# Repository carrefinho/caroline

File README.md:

# Caroline

Caroline is a 36-key unibody split electrostatic capacitive (EC) keyboard featuring Direct EC: the key matrix is read directly by the microcontroller's ADC, without using any external components.

> Her name is Caroline. Remember that!

> [!WARNING]
> This is a work in progress.

## Design

- Minimal BOM EC sensing: no mux, op-amp, integrator cap, no nothing
- 36-key Treadstone staggered layout with QAZlice characteristics
- Seeed Studio XIAO **Plus** controller on ZMK firmware
    - nRF52840 Plus for wireless, SAMD21 Plus or RP2040 Plus for wired
- Low-power wireless with nRF52840
    - Over a month of battery life on 100 mAh, a fraction of the power draw of other wireless EC keyboards
    - Idle scan draws under 30µA, always ready to type with no wake-up delay
- Plate designed for Deskeys (DES) housings

## Direct EC

## Files

- [`caroline-pcb/`](caroline-pcb/): KiCad project
    - [View the PCB on KiCanvas](https://kicanvas.org/?github=https%3A%2F%2Fgithub.com%2Fcarrefinho%2Fcaroline%2Ftree%2Fmain%2Fcaroline-pcb)
- [`ergogen/`](ergogen/): Ergogen config that generates key positions and reference outlines
- [`tools/`](tools/): helper scripts
    - [`pick_screws.py`](tools/pick_screws.py): picks optimal screw pattern for an even clamp (see [`caroline-pcb/`](caroline-pcb/README.md#screw-holes))

## Build Guide

## Firmware

## Credits

- [dohn-joh/heatwave](https://github.com/dohn-joh/heatwave): layout, aesthetics, ergogen reference
- [apfel/daertwing](https://git.clacktal.es/apfel/daertwing/): layout reference
- [Madeline](https://40s.wiki/boards/madeline): aesthetics
- [Marbelymarble/Adalyn](https://github.com/Marbelymarble/Adalyn): layout reference for early experiments

## License

[CERN-OHL-P v2](LICENSE)

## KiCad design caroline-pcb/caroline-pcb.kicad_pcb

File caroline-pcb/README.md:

# PCB

KiCad 10 project. Footprints, symbols and the XIAO 3D model are in [`lib/`](lib/).

## Screw holes

The PCB is screwed to the plate, clamping the housings and dome flanges between them, so where the screws go decides how evenly every key is clamped, which matters for EC since you want every dome to be equally snug against the PCB.

The board has 42 M2 holes, but only the 20 with a silk ring on the back are used. 20 seemed a reasonable compromise between an even clamp and ease of assembly. [`tools/pick_screws.py`](../tools/pick_screws.py) chose them. It tries every combination of holes, mirrored left to right, and keeps the one where keys and the outer edge are, on average, closest to a screw.

To re-pick, close the project in KiCad and run:

```sh
uv run tools/pick_screws.py -n 20 --apply
```

This moves the rings to the new picks on the board and in the schematic, and writes a plot comparing them to the current set.

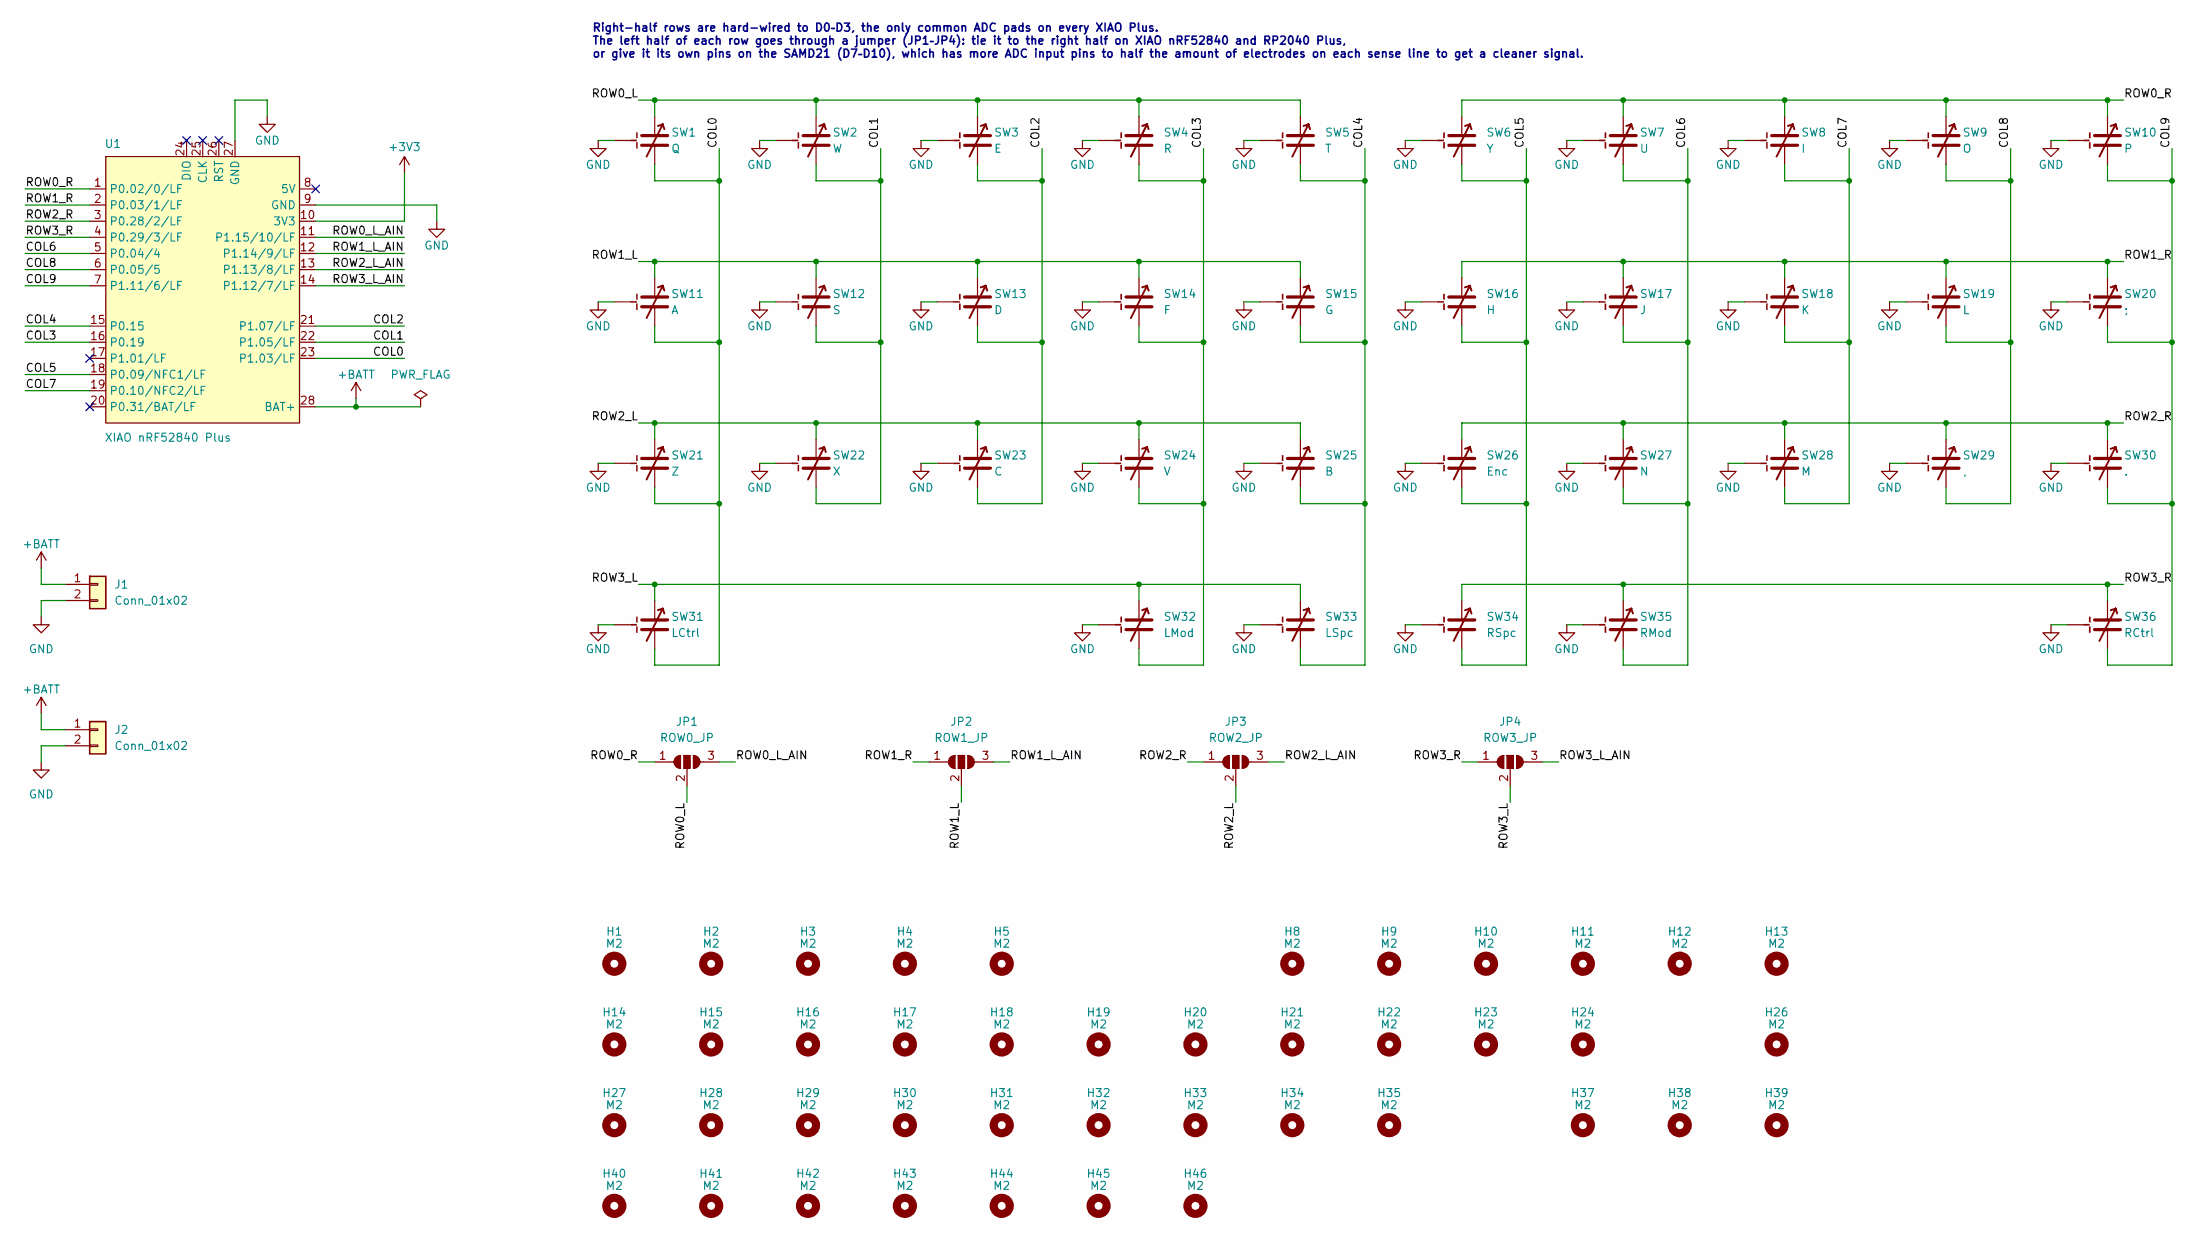
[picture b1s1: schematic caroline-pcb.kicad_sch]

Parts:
H1, H3, H5, H8, H10, H12, H15, H17, H20, H22, H26, H28, H33, H35, H37, H39, H41, H42, H44, H46: M2; MountingHole_2.2mm_M2_ring_silk
H2, H4, H9, H11, H13, H14, H16, H18, H19, H21, H23, H24, H27, H29, H30, H31, H32, H34, H38, H40, H43, H45: M2; MountingHole_2.2mm_M2
J1, J2: Conn_01x02; PinHeader_1x02_P2.54mm_Vertical
JP1: ROW0_JP; SolderJumper-3_P1.3mm_Open_RoundedPad1.0x1.5mm
JP2: ROW1_JP; SolderJumper-3_P1.3mm_Open_RoundedPad1.0x1.5mm
JP3: ROW2_JP; SolderJumper-3_P1.3mm_Open_RoundedPad1.0x1.5mm
JP4: ROW3_JP; SolderJumper-3_P1.3mm_Open_RoundedPad1.0x1.5mm
SW1: Q; EC_Topre_1U_ViaSP
SW2: W; EC_Topre_1U_ViaSP
SW3: E; EC_Topre_1U_ViaSP
SW4: R; EC_Topre_1U_ViaSP
SW5: T; EC_Topre_1U_ViaSP
SW6: Y; EC_Topre_1U_ViaSP
SW7: U; EC_Topre_1U_ViaSP
SW8: I; EC_Topre_1U_ViaSP
SW9: O; EC_Topre_1U_ViaSP
SW10: P; EC_Topre_1U_ViaSP
SW11: A; EC_Topre_1U_ViaSP
SW12: S; EC_Topre_1U_ViaSP
SW13: D; EC_Topre_1U_ViaSP
SW14: F; EC_Topre_1U_ViaSP
SW15: G; EC_Topre_1U_ViaSP
SW16: H; EC_Topre_1U_ViaSP
SW17: J; EC_Topre_1U_ViaSP
SW18: K; EC_Topre_1U_ViaSP
SW19: L; EC_Topre_1U_ViaSP
SW20: ;; EC_Topre_1U_ViaSP
SW21: Z; EC_Topre_1U_ViaSP
SW22: X; EC_Topre_1U_ViaSP
SW23: C; EC_Topre_1U_ViaSP
SW24: V; EC_Topre_1U_ViaSP
SW25: B; EC_Topre_1U_ViaSP
SW26: Enc; EC_Topre_1U_ViaSP
SW27: N; EC_Topre_1U_ViaSP
SW28: M; EC_Topre_1U_ViaSP
SW29: ,; EC_Topre_1U_ViaSP
SW30: .; EC_Topre_1U_ViaSP
SW31: LCtrl; EC_Topre_1U_ViaSP
SW32: LMod; EC_Topre_1U_ViaSP
SW33: LSpc; EC_Topre_1U_ViaSP
SW34: RSpc; EC_Topre_1U_ViaSP
SW35: RMod; EC_Topre_1U_ViaSP
SW36: RCtrl; EC_Topre_1U_ViaSP
U1: XIAO nRF52840 Plus; Xiao_nRF52840_Plus

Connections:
+3V3: U1.10 (3V3)
+BATT: J1.1, J2.1, U1.28 (BAT+)
/COL0: SW1.2, SW11.2, SW21.2, SW31.2, U1.23 (P1.03/LF)
/COL1: SW2.2, SW12.2, SW22.2, U1.22 (P1.05/LF)
/COL2: SW3.2, SW13.2, SW23.2, U1.21 (P1.07/LF)
/COL3: SW4.2, SW14.2, SW24.2, SW32.2, U1.16 (P0.19)
/COL4: SW5.2, SW15.2, SW25.2, SW33.2, U1.15 (P0.15)
/COL5: SW6.2, SW16.2, SW26.2, SW34.2, U1.18 (P0.09/NFC1/LF)
/COL6: SW7.2, SW17.2, SW27.2, SW35.2, U1.5 (P0.04/4)
/COL7: SW8.2, SW18.2, SW28.2, U1.19 (P0.10/NFC2/LF)
/COL8: SW9.2, SW19.2, SW29.2, U1.6 (P0.05/5)
/COL9: SW10.2, SW20.2, SW30.2, SW36.2, U1.7 (P1.11/6/LF)
/ROW0_L: JP1.2 (C), SW1.1 (S), SW2.1 (S), SW3.1 (S), SW4.1 (S), SW5.1 (S)
/ROW0_L_AIN: JP1.3 (B), U1.11 (P1.15/10/LF)
/ROW0_R: JP1.1 (A), SW6.1 (S), SW7.1 (S), SW8.1 (S), SW9.1 (S), SW10.1 (S), U1.1 (P0.02/0/LF)
/ROW1_L: JP2.2 (C), SW11.1 (S), SW12.1 (S), SW13.1 (S), SW14.1 (S), SW15.1 (S)
/ROW1_L_AIN: JP2.3 (B), U1.12 (P1.14/9/LF)
/ROW1_R: JP2.1 (A), SW16.1 (S), SW17.1 (S), SW18.1 (S), SW19.1 (S), SW20.1 (S), U1.2 (P0.03/1/LF)
/ROW2_L: JP3.2 (C), SW21.1 (S), SW22.1 (S), SW23.1 (S), SW24.1 (S), SW25.1 (S)
/ROW2_L_AIN: JP3.3 (B), U1.13 (P1.13/8/LF)
/ROW2_R: JP3.1 (A), SW26.1 (S), SW27.1 (S), SW28.1 (S), SW29.1 (S), SW30.1 (S), U1.3 (P0.28/2/LF)
/ROW3_L: JP4.2 (C), SW31.1 (S), SW32.1 (S), SW33.1 (S)
/ROW3_L_AIN: JP4.3 (B), U1.14 (P1.12/7/LF)
/ROW3_R: JP4.1 (A), SW34.1 (S), SW35.1 (S), SW36.1 (S), U1.4 (P0.29/3/LF)
GND: J1.2, J2.2, SW1.3 (D), SW2.3 (D), SW3.3 (D), SW4.3 (D), SW5.3 (D), SW6.3 (D), SW7.3 (D), SW8.3 (D), SW9.3 (D), SW10.3 (D), SW11.3 (D), SW12.3 (D), SW13.3 (D), SW14.3 (D), SW15.3 (D), SW16.3 (D), SW17.3 (D), SW18.3 (D), SW19.3 (D), SW20.3 (D), SW21.3 (D), SW22.3 (D), SW23.3 (D), SW24.3 (D), SW25.3 (D), SW26.3 (D), SW27.3 (D), SW28.3 (D), SW29.3 (D), SW30.3 (D), SW31.3 (D), SW32.3 (D), SW33.3 (D), SW34.3 (D), SW35.3 (D), SW36.3 (D), U1.9 (GND), U1.27 (GND)

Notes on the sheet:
Right-half rows are hard-wired to D0–D3, the only common ADC pads on every XIAO Plus. The left half of each row goes through a jumper (JP1–JP4): tie it to the right half on XIAO nRF52840 and RP2040 Plus, or give it its own pins on the SAMD21 (D7–D10), which has more ADC input pins to half the amoun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

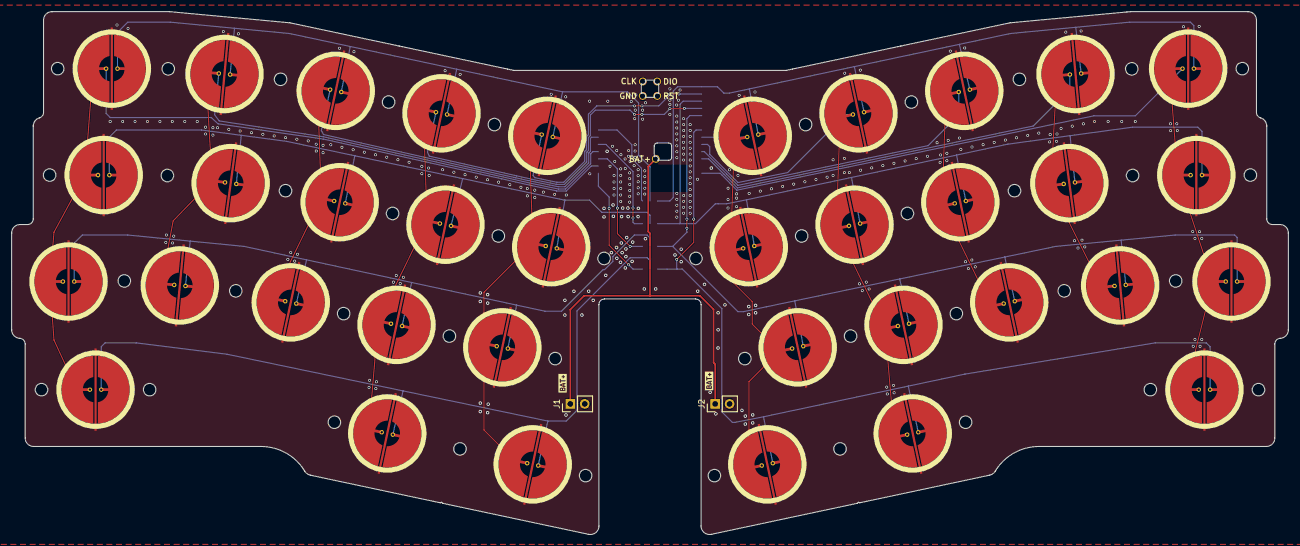
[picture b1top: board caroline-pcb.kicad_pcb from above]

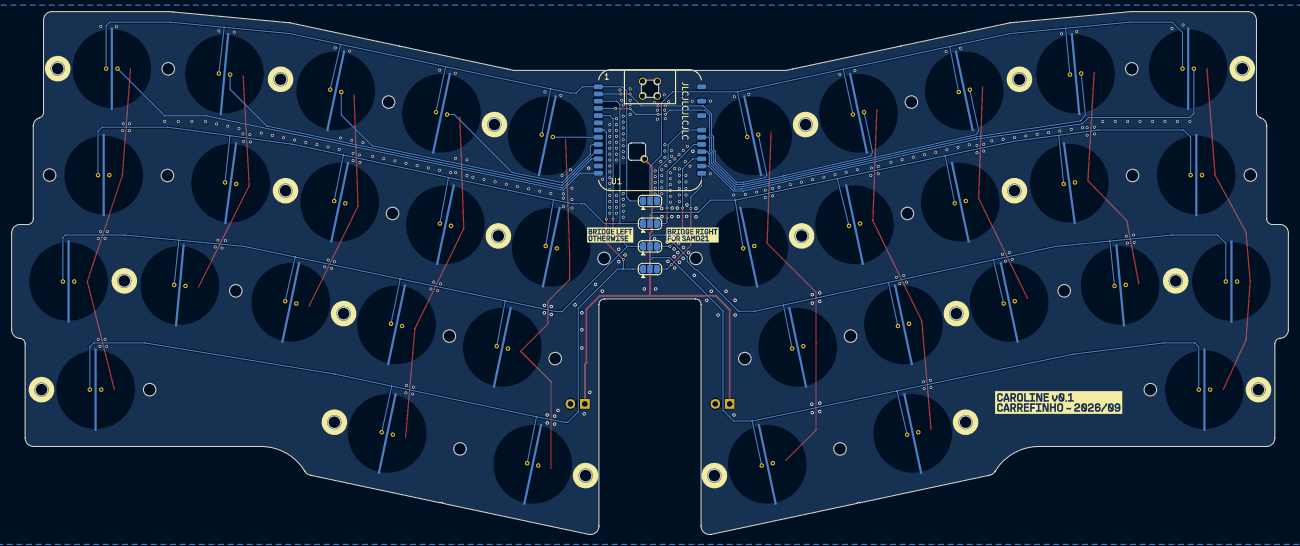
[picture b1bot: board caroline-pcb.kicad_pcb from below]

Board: 2 copper layers, 224.9 x 92.1 mm, 90 parts (50 on the bottom side), 24 nets.

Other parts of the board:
kibuzzard-6AB9B81E, kibuzzard-6AB9B81E#2: G***; kibuzzard-6AB9B81E
kibuzzard-6AB46F4A: G***; kibuzzard-6AB46F4A
kibuzzard-6AB46F64: G***; kibuzzard-6AB46F64
kibuzzard-6AB51704: G***; kibuzzard-6AB51704
